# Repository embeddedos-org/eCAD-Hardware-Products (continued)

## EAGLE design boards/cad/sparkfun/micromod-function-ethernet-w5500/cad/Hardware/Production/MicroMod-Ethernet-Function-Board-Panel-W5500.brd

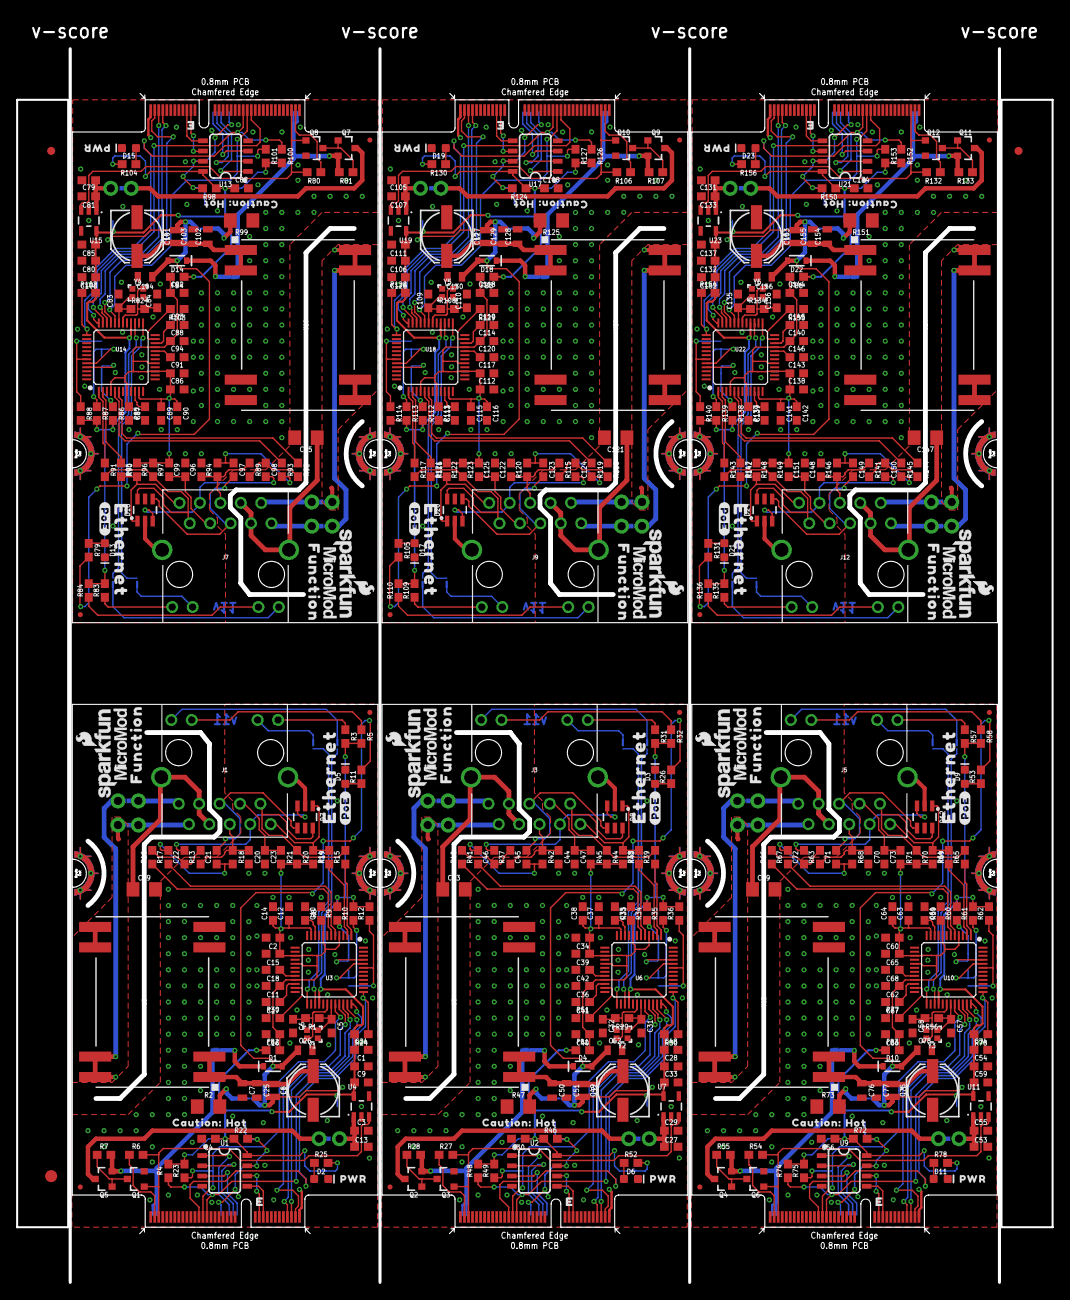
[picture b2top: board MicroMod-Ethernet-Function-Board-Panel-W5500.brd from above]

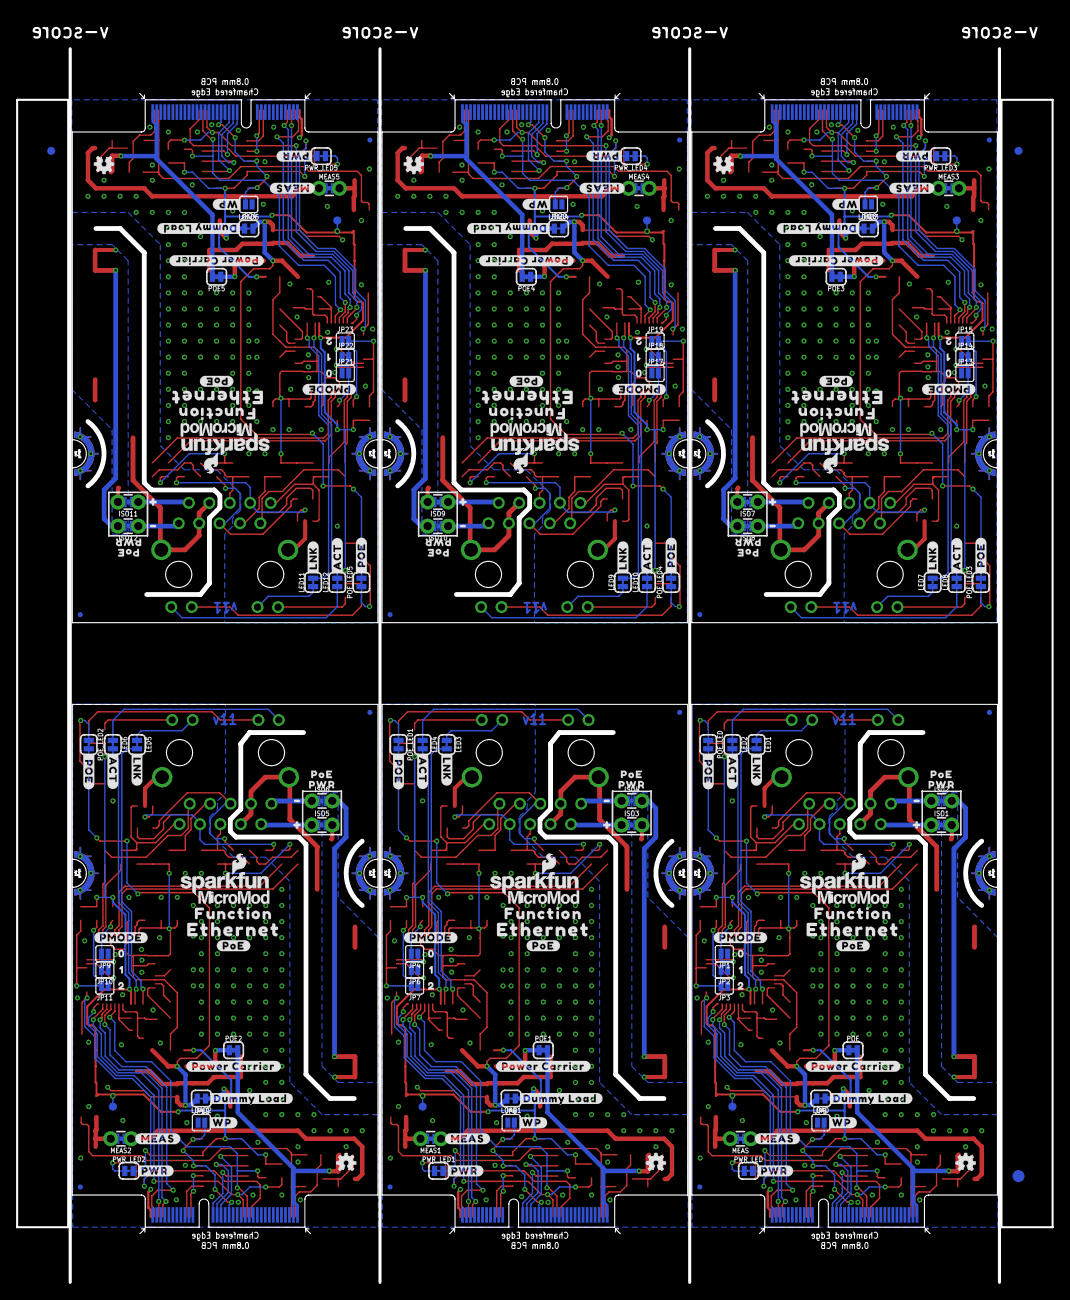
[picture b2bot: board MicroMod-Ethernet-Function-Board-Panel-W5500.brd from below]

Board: 2 copper layers, 128.7 x 153.4 mm, 696 parts (231 on the bottom side), 366 nets.

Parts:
C1, C2, C3, C4, C10, C11, C12, C14, C15, C28, C29, C30, C34, C35, C36, C37, C38, C39, C54, C55, C56, C60, C61, C62, C63, C64, C65, C80, C81, C82, C86, C87, C88, C89, C90, C91, C106, C107, C108, C112, C113, C114, C115, C116, C117, C132, C133, C134, C138, C139, C140, C141, C142, C143: 0.1uF; 0603
C5, C6, C31, C32, C57, C58, C83, C84, C109, C110, C135, C136: 10pF; 0603
C7, C25, C26, C50, C51, C52, C76, C77, C78, C102, C103, C104, C128, C129, C130, C154, C155, C156: 10uF; 0805
C8, C49, C75, C101, C127, C153: 100uF; PANASONIC_D
C9, C16, C33, C40, C59, C66, C85, C92, C111, C118, C137, C144: 10uF; 0603
C13, C24, C27, C48, C53, C74, C79, C100, C105, C126, C131, C152: 1.0uF; 0603
C17, C20, C41, C44, C67, C70, C93, C96, C119, C122, C145, C148: 10nF; 0603
C18, C42, C68, C94, C120, C146: 4.7uF; 0603
C19, C43, C69, C95, C121, C147: 1nF; 1206
C21, C22, C45, C46, C71, C72, C97, C98, C123, C124, C149, C150: 6.8nF; 0603
C23, C47, C73, C99, C125, C151: 22nF; 0603
D1, D4, D10, D14, D18, D22: 3A/10V/280mV; SOD-323
D2, D6, D11, D15, D19, D23: RED; LED-0603
D3, D5, D9, D13, D17, D21: Yellow; LED-0603
D7, D8, D12, D16, D20, D24: DT1042-04SO; SOT-23-6
E$1, E$2, E$3, E$4: FIDUCIAL-1X2
E$5, E$6: FIDUCIAL-1.5X3
FB1, FB2, FB3, FB4, FB5, FB6: 470Ω; 0603
FD1, FD2, FD3, FD4, FD5, FD6, FD7, FD8, FD9, FD10, FD11, FD12, FD13, FD14, FD15, FD16, FD17, FD18, FD19, FD20, FD21, FD22, FD23, FD24: FIDUCIALUFIDUCIAL; FIDUCIAL-MICRO
ISO1, ISO2, ISO3, ISO4, ISO5, ISO6, ISO7, ISO8, ISO9, ISO10, ISO11, ISO12: JUMPER-COMBO_2_NC_TRACE; COMBO-JUMPER_2_NC_TRACE
J1, J3, J5, J7, J9, J12: MAGJACK-POE; MAGJACK-SYM_LED
J2, J4, J6, J8, J10, J11: MICROMOD_STANDARD; M.2-CARD-E-22_FUNCTION_STANDARD
JP1, JP2, JP3, JP4, JP5, JP6, JP7, JP8, JP9, JP10, JP11, JP12, JP13, JP14, JP15, JP16, JP17, JP18, JP19, JP20, JP21, JP22, JP23, JP24: JUMPER-SMT_2_NO_SILK; SMT-JUMPER_2_NO_SILK
L1, L2, L3, L4, L5, L6: 2.2uH; 0805-WIDE
LED1, LED2, LED3, LED4, LED5, LED6, LED7, LED8, LED9, LED10, LED11, LED12: JUMPER-SMT_2_NC_TRACE_SILK; SMT-JUMPER_2_NC_TRACE_SILK
LOAD, LOAD1, LOAD2, LOAD3, LOAD4, LOAD5: JUMPER-SMT_2_NC_TRACE_SILK; SMT-JUMPER_2_NC_TRACE_SILK
LOGO1, LOGO2, LOGO4, LOGO6, LOGO7, LOGO9, LOGO10, LOGO12, LOGO13, LOGO15, LOGO16, LOGO18: SFE_LOGO_NAME_FLAME.1_INCH; SFE_LOGO_NAME_FLAME_.1
LOGO3, LOGO5, LOGO8, LOGO11, LOGO14, LOGO17: OSHW-LOGOMINI; OSHW-LOGO-MINI
MEAS, MEAS1, MEAS2, MEAS3, MEAS4, MEAS5: JUMPER-COMBO_2_NC_TRACE; COMBO-JUMPER_2_NC_TRACE
POE, POE1, POE2, POE3, POE4, POE5: SMT-JUMPER_2_NC_TRACE_SILK
POE_LED, POE_LED1, POE_LED2, POE_LED3, POE_LED4, POE_LED5: JUMPER-SMT_2_NC_TRACE_SILK; SMT-JUMPER_2_NC_TRACE_SILK
PWR_LED, PWR_LED1, PWR_LED2, PWR_LED3, PWR_LED4, PWR_LED5: JUMPER-SMT_2_NC_TRACE_SILK; SMT-JUMPER_2_NC_TRACE_SILK
Q1, Q3, Q6, Q8, Q10, Q12: 220mA/50V/3.5Ω; SOT23-3
Q2, Q4, Q5, Q7, Q9, Q11: 20V/4.2A/52mΩ/1.4W; SOT23-3
R1, R29, R56, R82, R108, R134: 1M; 0603
R2, R47, R73, R99, R125, R151: 49.9 1/2W; 1206
R3, R5, R11, R25, R26, R31, R32, R52, R53, R57, R58, R78, R79, R83, R84, R104, R105, R109, R110, R130, R131, R135, R136, R156: 1k; 0603
R4, R6, R7, R9, R10, R12, R22, R23, R24, R27, R28, R30, R34, R35, R36, R46, R48, R49, R50, R51, R54, R55, R60, R61, R62, R72, R74, R75, R76, R77, R80, R81, R86, R87, R88, R98, R100, R101, R102, R103, R106, R107, R112, R113, R114, R124, R126, R127, R128, R129, R132, R133, R138, R139, R140, R150, R152, R153, R154, R155: 10k; 0603
R8, R33, R59, R85, R111, R137: 12.4k; 0603
R13, R18, R19, R20, R37, R42, R43, R44, R63, R68, R69, R70, R89, R94, R95, R96, R115, R120, R121, R122, R141, R146, R147, R148: 49.9; 0603
R14, R15, R16, R17, R38, R39, R40, R41, R64, R65, R66, R67, R90, R91, R92, R93, R116, R117, R118, R119, R142, R143, R144, R145: 33; 0603
R21, R45, R71, R97, R123, R149: 10; 0603
TP1, TP2, TP3, TP4, TP5, TP6: TEST-POINT3X4; PAD.03X.04
U1, U2, U9, U13, U17, U21: EEPROM; SO08
U3, U6, U10, U14, U18, U22: W5500; LQFP-48
U4, U7, U11, U15, U19, U23: 3.3V; SOT23-5
U5, U8, U12, U16, U20, U24: POE_PSU-DP990X; DP990X
U$1, U$17, U$34, U$36, U$62, U$65, U$90, U$92, U$117, U$119, U$144, U$146: ETHERNET0
U$2, U$18, U$35, U$38, U$64, U$66, U$91, U$93, U$118, U$120, U$145, U$147: #POE#0
U$3, U$39, U$67, U$94, U$121, U$148: #POWER_CARRIER#0
U$4, U$10, U$37, U$54, U$55, U$63, U$82, U$83, U$109, U$110, U$136, U$137: MICROMOD_LOGO_.35
U$5, U$40, U$68, U$95, U$122, U$149: #DUMMY_LOAD#0
U$6, U$41, U$69, U$96, U$123, U$150: #WP#0
U$7, U$29, U$57, U$85, U$112, U$139: PWR0
U$8, U$42, U$70, U$97, U$124, U$151: #ACT#0
U$9, U$48, U$76, U$103, U$130, U$157: POE0
U$11, U$28, U$56, U$84, U$111, U$138: #MEAS#3
U$12, U$43, U$71, U$98, U$125, U$152: #LNK#1
U$13, U$30, U$58, U$86, U$113, U$140: #PMODE#0
U$14, U$31, U$59, U$87, U$114, U$141: 01
U$15, U$32, U$60, U$88, U$115, U$142: 12
U$16, U$33, U$61, U$89, U$116, U$143: 23
U$19, U$50, U$78, U$105, U$132, U$159: #0
U$20, U$44, U$72, U$99, U$126, U$153: CAUTION#0
U$21, U$45, U$73, U$100, U$127, U$154: HOT#1
U$22, U$46, U$74, U$101, U$128, U$155: #PWR#0
U$23, U$47, U$75, U$102, U$129, U$156: #_POE#0
U$24, U$49, U$77, U$104, U$131, U$158: PWR1
U$25, U$51, U$79, U$106, U$133, U$160: #1
U$26, U$27, U$52, U$53, U$80, U$81, U$107, U$108, U$134, U$135, U$161, U$162: FUNCTION0
Y1, Y2, Y3, Y4, Y5, Y6: 25MHz; CRYSTAL-SMD-2.0X1.6MM

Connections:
3.3V: C1.1, C4.1, C9.1, C24.1, FB2.1, PWR_LED.2, R3.2, R4.2, R5.2, R9.2, R10.2, R12.2, R22.1, R23.2, R24.2, TP1.1, U1.8, U3.28, U4.5
3.3V1: C28.1, C30.1, C33.1, C48.1, FB1.1, PWR_LED1.2, R31.2, R32.2, R34.2, R35.2, R36.2, R46.1, R48.2, R49.2, R50.2, TP2.1, U2.8, U6.28, U7.5
3.3V2: C54.1, C56.1, C59.1, C74.1, FB3.1, PWR_LED2.2, R57.2, R58.2, R60.2, R61.2, R62.2, R72.1, R74.2, R75.2, R76.2, TP3.1, U9.8, U10.28, U11.5
3.3V3: C80.1, C82.1, C85.1, C100.1, FB4.1, PWR_LED3.2, R83.2, R84.2, R86.2, R87.2, R88.2, R98.1, R100.2, R101.2, R102.2, TP4.1, U13.8, U14.28, U15.5
3.3V4: C106.1, C108.1, C111.1, C126.1, FB5.1, PWR_LED4.2, R109.2, R110.2, R112.2, R113.2, R114.2, R124.1, R126.2, R127.2, R128.2, TP5.1, U17.8, U18.28, U19.5
3.3V5: C132.1, C134.1, C137.1, C152.1, FB6.1, PWR_LED5.2, R135.2, R136.2, R138.2, R139.2, R140.2, R150.1, R152.2, R153.2, R154.2, TP6.1, U21.8, U22.28, U23.5
3.3V_IN: J11.73, R6.1
3.3V_IN1: J2.73, R27.1
3.3V_IN2: J4.73, R54.1
3.3V_IN3: J6.73, R80.1
3.3V_IN4: J8.73, R106.1
3.3V_IN5: J10.73, R132.1
5V: C3.1, C13.1, MEAS.2, MEAS.4, U4.1
5V1: C27.1, C29.1, MEAS1.2, MEAS1.4, U7.1
5V2: C53.1, C55.1, MEAS2.2, MEAS2.4, U11.1
5V3: C79.1, C81.1, MEAS3.2, MEAS3.4, U15.1
5V4: C105.1, C107.1, MEAS4.2, MEAS4.4, U19.1
5V5: C131.1, C133.1, MEAS5.2, MEAS5.4, U23.1
5V_FILTER: C26.1, D1.A, L1.2, LOAD.2, POE_LED.2
5V_FILTER1: C52.1, D4.A, L2.2, LOAD1.2, POE_LED1.2
5V_FILTER2: C78.1, D10.A, L3.2, LOAD2.2, POE_LED2.2
5V_FILTER3: C104.1, D14.A, L4.2, LOAD3.2, POE_LED3.2
5V_FILTER4: C130.1, D18.A, L5.2, LOAD4.2, POE_LED4.2
5V_FILTER5: C156.1, D22.A, L6.2, LOAD5.2, POE_LED5.2
5V_RAW: C7.1, C8.+, C25.1, L1.1, U5.1, U5.2
5V_RAW1: C49.+, C50.1, C51.1, L2.1, U8.1, U8.2
5V_RAW2: C75.+, C76.1, C77.1, L3.1, U12.1, U12.2
5V_RAW3: C101.+, C102.1, C103.1, L4.1, U16.1, U16.2
5V_RAW4: C127.+, C128.1, C129.1, L5.1, U20.1, U20.2
5V_RAW5: C153.+, C154.1, C155.1, L6.1, U24.1, U24.2
A0: J11.36, U1.1
A1: J11.34, U1.2
A2: J11.32, U1.3
A3: J2.36, U2.1
A4: J2.32, U2.3
A5: J2.34, U2.2
A6: J4.36, U9.1
A7: J4.32, U9.3
A8: J4.34, U9.2
A9: J6.36, U13.1
A10: J6.32, U13.3
A11: J6.34, U13.2
A12: J8.36, U17.1
A13: J8.32, U17.3
A14: J8.34, U17.2
A15: J10.36, U21.1
A16: J10.32, U21.3
A17: J10.34, U21.2
ACT_LED: LED2.2, U3.27
ACT_LED1: LED4.2, U6.27
ACT_LED2: LED6.2, U10.27
ACT_LED3: LED8.2, U14.27
ACT_LED4: LED10.2, U18.27
ACT_LED5: LED12.2, U22.27
ETH_!CS!: J11.49, R23.1, U3.32
ETH_!CS!1: J2.49, R49.1, U6.32
ETH_!CS!2: J4.49, R75.1, U10.32
ETH_!CS!3: J6.49, R101.1, U14.32
ETH_!CS!4: J8.49, R127.1, U18.32
ETH_!CS!5: J10.49, R153.1, U22.32
ETH_!INT!: J11.47, R4.1, U3.36
ETH_!INT!1: J2.47, R48.1, U6.36
ETH_!INT!2: J4.47, R74.1, U10.36
ETH_!INT!3: J6.47, R100.1, U14.36
ETH_!INT!4: J8.47, R126.1, U18.36
ETH_!INT!5: J10.47, R152.1, U22.36
ETH_!RST!: J11.51, R24.1, U3.37
ETH_!RST!1: J2.51, R50.1, U6.37
ETH_!RST!2: J4.51, R76.1, U10.37
ETH_!RST!3: J6.51, R102.1, U14.37
ETH_!RST!4: J8.51, R128.1, U18.37
ETH_!RST!5: J10.51, R154.1, U22.37
EWP: J11.40, JP5.2, R22.2, U1.7
EWP1: J2.40, JP8.2, R46.2, U2.7
EWP2: J4.40, JP12.2, R72.2, U9.7
EWP3: J6.40, JP16.2, R98.2, U13.7
EWP4: J8.40, JP20.2, R124.2, U17.7
EWP5: J10.40, JP24.2, R150.2, U21.7
GND: C1.2, C2.2, C3.2, C4.2, C5.2, C6.2, C7.2, C8.-, C9.2, C10.2, C11.2, C12.2, C13.2, C14.2, C15.2, C16.2, C17.2, C18.2, C19.2, C20.2, C23.2, C24.2, C25.2, C26.2, D2.C, D5.C, J11.1, J11.33, J11.39, J11.45, J11.75, J11.GND1, J11.GND2, J11.GND3, J11.GND4, J11.GND5, J11.GND6, JP1.1, JP2.1, JP3.1, JP5.1, Q1.2, R2.1, R8.1, R30.1, U1.4, U3.3, U3.9, U3.14, U3.16, U3.19, U3.29, U3.48, U4.2, U5.3
GND1: C27.2, C28.2, C29.2, C30.2, C31.2, C32.2, C33.2, C34.2, C35.2, C36.2, C37.2, C38.2, C39.2, C40.2, C41.2, C42.2, C43.2, C44.2, C47.2, C48.2, C49.-, C50.2, C51.2, C52.2, D3.C, D6.C, J2.1, J2.33, J2.39, J2.45, J2.75, J2.GND1, J2.GND2, J2.GND3, J2.GND4, J2.GND5, J2.GND6, JP4.1, JP6.1, JP7.1, JP8.1, Q3.2, R33.1, R47.1, R51.1, U2.4, U6.3, U6.9, U6.14, U6.16, U6.19, U6.29, U6.48, U7.2, U8.3
GND2: C53.2, C54.2, C55.2, C56.2, C57.2, C58.2, C59.2, C60.2, C61.2, C62.2, C63.2, C64.2, C65.2, C66.2, C67.2, C68.2, C69.2, C70.2, C73.2, C74.2, C75.-, C76.2, C77.2, C78.2, D9.C, D11.C, J4.1, J4.33, J4.39, J4.45, J4.75, J4.GND1, J4.GND2, J4.GND3, J4.GND4, J4.GND5, J4.GND6, JP9.1, JP10.1, JP11.1, JP12.1, Q6.2, R59.1, R73.1, R77.1, U9.4, U10.3, U10.9, U10.14, U10.16, U10.19, U10.29, U10.48, U11.2, U12.3
GND3: C79.2, C80.2, C81.2, C82.2, C83.2, C84.2, C85.2, C86.2, C87.2, C88.2, C89.2, C90.2, C91.2, C92.2, C93.2, C94.2, C95.2, C96.2, C99.2, C100.2, C101.-, C102.2, C103.2, C104.2, D13.C, D15.C, J6.1, J6.33, J6.39, J6.45, J6.75, J6.GND1, J6.GND2, J6.GND3, J6.GND4, J6.GND5, J6.GND6, JP13.1, JP14.1, JP15.1, JP16.1, Q8.2, R85.1, R99.1, R103.1, U13.4, U14.3, U14.9, U14.14, U14.16, U14.19, U14.29, U14.48, U15.2, U16.3
GND4: C105.2, C106.2, C107.2, C108.2, C109.2, C110.2, C111.2, C112.2, C113.2, C114.2, C115.2, C116.2, C117.2, C118.2, C119.2, C120.2, C121.2, C122.2, C125.2, C126.2, C127.-, C128.2, C129.2, C130.2, D17.C, D19.C, J8.1, J8.33, J8.39, J8.45, J8.75, J8.GND1, J8.GND2, J8.GND3, J8.GND4, J8.GND5, J8.GND6, JP17.1, JP18.1, JP19.1, JP20.1, Q10.2, R111.1, R125.1, R129.1, U17.4, U18.3, U18.9, U18.14, U18.16, U18.19, U18.29, U18.48, U19.2, U20.3
GND5: C131.2, C132.2, C133.2, C134.2, C135.2, C136.2, C137.2, C138.2, C139.2, C140.2, C141.2, C142.2, C143.2, C144.2, C145.2, C146.2, C147.2, C148.2, C151.2, C152.2, C153.-, C154.2, C155.2, C156.2, D21.C, D23.C, J10.1, J10.33, J10.39, J10.45, J10.75, J10.GND1, J10.GND2, J10.GND3, J10.GND4, J10.GND5, J10.GND6, JP21.1, JP22.1, JP23.1, JP24.1, Q12.2, R137.1, R151.1, R155.1, U21.4, U22.3, U22.9, U22.14, U22.16, U22.19, U22.29, U22.48, U23.2, U24.3
GND-ISO: C19.1, D7.2, J1.7, J1.8, J1.S1, J1.S2
GND-ISO1: C43.1, D8.2, J3.7, J3.8, J3.S1, J3.S2
GND-ISO2: C69.1, D12.2, J5.7, J5.8, J5.S1, J5.S2
GND-ISO3: C95.1, D16.2, J7.7, J7.8, J7.S1, J7.S2
GND-ISO4: C121.1, D20.2, J9.7, J9.8, J9.S1, J9.S2
GND-ISO5: C147.1, D24.2, J12.7, J12.8, J12.S1, J12.S2
I2C_SCL: J11.21, U1.6
I2C_SCL1: J2.21, U2.6
I2C_SCL2: J4.21, U9.6
I2C_SCL3: J6.21, U13.6
I2C_SCL4: J8.21, U17.6
I2C_SCL5: J10.21, U21.6
I2C_SDA: J11.19, U1.5
I2C_SDA1: J2.19, U2.5
I2C_SDA2: J4.19, U9.5
I2C_SDA3: J6.19, U13.5
I2C_SDA4: J8.19, U17.5
I2C_SDA5: J10.19, U21.5
LINK_LED: LED1.2, U3.25
LINK_LED1: LED3.2, U6.25
LINK_LED2: LED5.2, U10.25
LINK_LED3: LED7.2, U14.25
LINK_LED4: LED9.2, U18.25
LINK_LED5: LED11.2, U22.25
unnamed: C5.1, R1.1, U3.31, Y1.1
unnamed: C6.1, R1.2, U3.30, Y1.3
unnamed: J1.14, LED2.1
unnamed: J1.12, LED1.1
unnamed: D5.A, R11.1
unnamed: POE_LED.1, R11.2
unnamed: D1.C, POE.1
unnamed: J1.13, R5.1
unnamed: LOAD.1, R2.2
unnamed: J1.11, R3.1
unnamed: Q1.3, Q5.1, R7.1
unnamed: POE_LED1.1, R26.2
unnamed: R8.2, U3.10
unnamed: D3.A, R26.1
unnamed: C17.1, U3.22
unnamed: C18.1, U3.20
unnamed: R30.2, U3.23
unnamed: Q2.1, Q3.3, R28.1
unnamed: PWR_LED.1, R25.2
unnamed: D2.A, R25.1
unnamed: C31.1, R29.1, U6.31, Y2.1
unnamed: C32.1, R29.2, U6.30, Y2.3
unnamed: J3.13, R32.1
unnamed: J3.11, R31.1
unnamed: R33.2, U6.10
unnamed: C41.1, U6.22
unnamed: C42.1, U6.20
unnamed: D4.C, POE1.1
unnamed: LOAD1.1, R47.2
unnamed: J3.12, LED3.1
unnamed: J3.14, LED4.1
unnamed: R51.2, U6.23
unnamed: PWR_LED1.1, R52.2
unnamed: D6.A, R52.1
unnamed: POE_LED2.1, R53.2
unnamed: D9.A, R53.1
unnamed: Q4.1, Q6.3, R55.1
unnamed: C57.1, R56.1, U10.31, Y3.1
unnamed: C58.1, R56.2, U10.30, Y3.3
unnamed: J5.13, R58.1
unnamed: J5.11, R57.1
unnamed: R59.2, U10.10
unnamed: C67.1, U10.22
unnamed: C68.1, U10.20
unnamed: D10.C, POE2.1
unnamed: LOAD2.1, R73.2
unnamed: J5.12, LED5.1
unnamed: J5.14, LED6.1
unnamed: R77.2, U10.23
unnamed: PWR_LED2.1, R78.2
unnamed: D11.A, R78.1
unnamed: POE_LED3.1, R79.2
unnamed: D13.A, R79.1
unnamed: Q7.1, Q8.3, R81.1
unnamed: C83.1, R82.1, U14.31, Y4.1
unnamed: C84.1, R82.2, U14.30, Y4.3
unnamed: J7.13, R84.1
unnamed: J7.11, R83.1
unnamed: R85.2, U14.10
unnamed: C93.1, U14.22
unnamed: C94.1, U14.20
unnamed: D14.C, POE3.1
unnamed: LOAD3.1, R99.2
unnamed: J7.12, LED7.1
unnamed: J7.14, LED8.1
unnamed: R103.2, U14.23
unnamed: PWR_LED3.1, R104.2
unnamed: D15.A, R104.1
unnamed: POE_LED4.1, R105.2
unnamed: D17.A, R105.1
unnamed: Q9.1, Q10.3, R107.1
unnamed: C109.1, R108.1, U18.31, Y5.1
unnamed: C110.1, R108.2, U18.30, Y5.3
unnamed: J9.13, R110.1
unnamed: J9.11, R109.1
unnamed: R111.2, U18.10
unnamed: C119.1, U18.22
unnamed: C120.1, U18.20
unnamed: D18.C, POE4.1
unnamed: LOAD4.1, R125.2
unnamed: J9.12, LED9.1
unnamed: J9.14, LED10.1
unnamed: R129.2, U18.23
unnamed: PWR_LED4.1, R130.2
unnamed: D19.A, R130.1
unnamed: POE_LED5.1, R131.2
unnamed: D21.A, R131.1
unnamed: Q11.1, Q12.3, R133.1
unnamed: C135.1, R134.1, U22.31, Y6.1
unnamed: C136.1, R134.2, U22.30, Y6.3
unnamed: J12.13, R136.1
unnamed: J12.11, R135.1
unnamed: R137.2, U22.10
unnamed: C145.1, U22.22
unnamed: C146.1, U22.20
unnamed: D22.C, POE5.1
unnamed: LOAD5.1, R151.2
unnamed: J12.12, LED11.1
unnamed: J12.14, LED12.1
unnamed: R155.2, U22.23
unnamed: PWR_LED5.1, R156.2
unnamed: D23.A, R156.1
PMODE0: JP1.2, R9.1, U3.45
PMODE1: JP2.2, R10.1, U3.44
PMODE2: JP3.2, R12.1, U3.43
PMODE3: JP4.2, R34.1, U6.45
PMODE4: JP6.2, R35.1, U6.44
PMODE5: JP7.2, R36.1, U6.43
PMODE6: JP9.2, R60.1, U10.45
PMODE7: JP10.2, R61.1, U10.44
PMODE8: JP11.2, R62.1, U10.43
PMODE9: JP13.2, R86.1, U14.45
PMODE10: JP14.2, R87.1, U14.44
PMODE11: JP15.2, R88.1, U14.43
PMODE12: JP17.2, R112.1, U18.45
PMODE13: JP18.2, R113.1, U18.44
PMODE14: JP19.2, R114.1, U18.43
PMODE15: JP21.2, R138.1, U22.45
PMODE16: JP22.2, R139.1, U22.44
PMODE17: JP23.2, R140.1, U22.43
PW1+: ISO1.2, ISO1.4, U5.5, U5.6
PW1+1: ISO3.2, ISO3.4, U8.5, U8.6
PW1+2: ISO5.2, ISO5.4, U12.5, U12.6
PW1+3: ISO7.2, ISO7.4, U16.5, U16.6
PW1+4: ISO9.2, ISO9.4, U20.5, U20.6
PW1+5: ISO11.2, ISO11.4, U24.5, U24.6
PW1-: ISO2.2, ISO2.4, U5.7, U5.8
PW1-1: ISO4.2, ISO4.4, U8.7, U8.8
PW1-2: ISO6.2, ISO6.4, U12.7, U12.8
PW1-3: ISO8.2, ISO8.4, U16.7, U16.8
PW1-4: ISO10.2, ISO10.4, U20.7, U20.8
PW1-5: ISO12.2, ISO12.4, U24.7, U24.8
PW+: ISO1.1, ISO1.3, J1.9
PW+1: ISO3.1, ISO3.3, J3.9
PW+2: ISO5.1, ISO5.3, J5.9
PW+3: ISO7.1, ISO7.3, J7.9
PW+4: ISO9.1, ISO9.3, J9.9
PW+5: ISO11.1, ISO11.3, J12.9
PW-: ISO2.1, ISO2.3, J1.10
PW-1: ISO4.1, ISO4.3, J3.10
PW-2: ISO6.1, ISO6.3, J5.10
PW-3: ISO8.1, ISO8.3, J7.10
PW-4: ISO10.1, ISO10.3, J9.10
PW-5: ISO12.1, ISO12.3, J12.10
PWR_EN: J11.71, Q1.1, R6.2, U4.3
PWR_EN1: J2.71, Q3.1, R27.2, U7.3
PWR_EN2: J4.71, Q6.1, R54.2, U11.3
PWR_EN3: J6.71, Q8.1, R80.2, U15.3
PWR_EN4: J8.71, Q10.1, R106.2, U19.3
PWR_EN5: J10.71, Q12.1, R132.2, U23.3
RCT: C20.1, J1.5, R13.1, R18.1
RCT1: C44.1, J3.5, R37.1, R42.1
RCT2: C70.1, J5.5, R63.1, R68.1
RCT3: C96.1, J7.5, R89.1, R94.1
RCT4: C122.1, J9.5, R115.1, R120.1
RCT5: C148.1, J12.5, R141.1, R146.1
RD+: C22.2, D7.3, J1.3
RD+1: C46.2, D8.3, J3.3
RD+2: C72.2, D12.3, J5.3
RD+3: C98.2, D16.3, J7.3
RD+4: C124.2, D20.3, J9.3
RD+5: C150.2, D24.3, J12.3
RD-: C21.2, D7.4, J1.6
RD-1: C45.2, D8.4, J3.6
RD-2: C71.2, D12.4, J5.6
RD-3: C97.2, D16.4, J7.6
RD-4: C123.2, D20.4, J9.6
RD-5: C149.2, D24.4, J12.6
RXN: R17.1, U3.5
RXN1: C21.1, R17.2, R18.2
RXN2: R41.1, U6.5
RXN3: C45.1, R41.2, R42.2
RXN4: R67.1, U10.5
RXN5: C71.1, R67.2, R68.2
RXN6: R93.1, U14.5
RXN7: C97.1, R93.2, R94.2
RXN8: R119.1, U18.5
RXN9: C123.1, R119.2, R120.2
RXN10: R145.1, U22.5
RXN11: C149.1, R145.2, R146.2
RXP: R16.1, U3.6
RXP1: C22.1, R13.2, R16.2
RXP2: R40.1, U6.6
RXP3: C46.1, R37.2, R40.2
RXP4: R66.1, U10.6
RXP5: C72.1, R63.2, R66.2
RXP6: R92.1, U14.6
RXP7: C98.1, R89.2, R92.2
RXP8: R118.1, U18.6
RXP9: C124.1, R115.2, R118.2
RXP10: R144.1, U22.6
RXP11: C150.1, R141.2, R144.2
SPI_CIPO: J11.7, U3.34
SPI_CIPO1: J2.7, U6.34
SPI_CIPO2: J4.7, U10.34
SPI_CIPO3: J6.7, U14.34
SPI_CIPO4: J8.7, U18.34
SPI_CIPO5: J10.7, U22.34
SPI_COPI: J11.5, U3.35
SPI_COPI1: J2.5, U6.35
SPI_COPI2: J4.5, U10.35
SPI_COPI3: J6.5, U14.35
SPI_COPI4: J8.5, U18.35
SPI_COPI5: J10.5, U22.35
SPI_SCK: J11.3, U3.33
SPI_SCK1: J2.3, U6.33
SPI_SCK2: J4.3, U10.33
SPI_SCK3: J6.3, U14.33
SPI_SCK4: J8.3, U18.33
SPI_SCK5: J10.3, U22.33
TCT: C23.1, J1.4, R21.1
TCT1: C47.1, J3.4, R45.1
TCT2: C73.1, J5.4, R71.1
TCT3: C99.1, J7.4, R97.1
TCT4: C125.1, J9.4, R123.1
TCT5: C151.1, J12.4, R149.1
TD+: D7.1, J1.1, R14.2, R19.1
TD+1: D8.1, J3.1, R38.2, R43.1
TD+2: D12.1, J5.1, R64.2, R69.1
TD+3: D16.1, J7.1, R90.2, R95.1
TD+4: D20.1, J9.1, R116.2, R121.1
TD+5: D24.1, J12.1, R142.2, R147.1
TD-: D7.6, J1.2, R15.2, R20.1
TD-1: D8.6, J3.2, R39.2, R44.1
TD-2: D12.6, J5.2, R65.2, R70.1
TD-3: D16.6, J7.2, R91.2, R96.1
TD-4: D20.6, J9.2, R117.2, R122.1
TD-5: D24.6, J12.2, R143.2, R148.1
TXN: R15.1, U3.1
TXN1: R39.1, U6.1
TXN2: R65.1, U10.1
TXN3: R91.1, U14.1
TXN4: R117.1, U18.1
TXN5: R143.1, U22.1
TXP: R14.1, U3.2
TXP1: R38.1, U6.2
TXP2: R64.1, U10.2
TXP3: R90.1, U14.2
TXP4: R116.1, U18.2
TXP5: R142.1, U22.2
VCC: MEAS.1, MEAS.3, Q5.3
VCC1: MEAS1.1, MEAS1.3, Q2.3
VCC2: MEAS2.1, MEAS2.3, Q4.3
VCC3: MEAS3.1, MEAS3.3, Q7.3
VCC4: MEAS4.1, MEAS4.3, Q9.3
VCC5: MEAS5.1, MEAS5.3, Q11.3
VCCA: C2.1, C10.1, C11.1, C12.1, C14.1, C15.1, C16.1, FB2.2, R19.2, R20.2, R21.2, U3.4, U3.8, U3.11, U3.15, U3.17, U3.21
VCCA1: C34.1, C35.1, C36.1, C37.1, C38.1, C39.1, C40.1, FB1.2, R43.2, R44.2, R45.2, U6.4, U6.8, U6.11, U6.15, U6.17, U6.21
VCCA2: C60.1, C61.1, C62.1, C63.1, C64.1, C65.1, C66.1, FB3.2, R69.2, R70.2, R71.2, U10.4, U10.8, U10.11, U10.15, U10.17, U10.21
VCCA3: C86.1, C87.1, C88.1, C89.1, C90.1, C91.1, C92.1, FB4.2, R95.2, R96.2, R97.2, U14.4, U14.8, U14.11, U14.15, U14.17, U14.21
VCCA4: C112.1, C113.1, C114.1, C115.1, C116.1, C117.1, C118.1, FB5.2, R121.2, R122.2, R123.2, U18.4, U18.8, U18.11, U18.15, U18.17, U18.21
VCCA5: C138.1, C139.1, C140.1, C141.1, C142.1, C143.1, C144.1, FB6.2, R147.2, R148.2, R149.2, U22.4, U22.8, U22.11, U22.15, U22.17, U22.21
VCC_IN: J11.72, J11.74, POE.2, Q5.2, R7.2
VCC_IN1: J2.72, J2.74, POE1.2, Q2.2, R28.2
VCC_IN2: J4.72, J4.74, POE2.2, Q4.2, R55.2
VCC_IN3: J6.72, J6.74, POE3.2, Q7.2, R81.2
VCC_IN4: J8.72, J8.74, POE4.2, Q9.2, R107.2
VCC_IN5: J10.72, J10.74, POE5.2, Q11.2, R133.2

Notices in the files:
parts and their libraries:
SparkFun-Aesthetics: Licensing: Creative Commons ShareAlike 4.0 International - https://creativecommons.org/licenses/by-sa/4.0
SparkFun-Aesthetics: Released under the Creative Commons Attribution Share-Alike 4.0 License
SparkFun-Aesthetics: https://creativecommons.org/licenses/by-sa/4.0
